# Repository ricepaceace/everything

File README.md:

# everything
Each folder in this directory contains all the files for the separate areas of our project.
matlab_algorithms     contains all of the data and matlab code for running simulations of our developing algorithm
analogTest            contains the design of our artificial anaolg input generator
Arduino               contains all the code and test data used by the Arduino microcontroller
preprocessor_harware  contains the design of our preprocessor boards
xilinx_design         contains the FPGA design

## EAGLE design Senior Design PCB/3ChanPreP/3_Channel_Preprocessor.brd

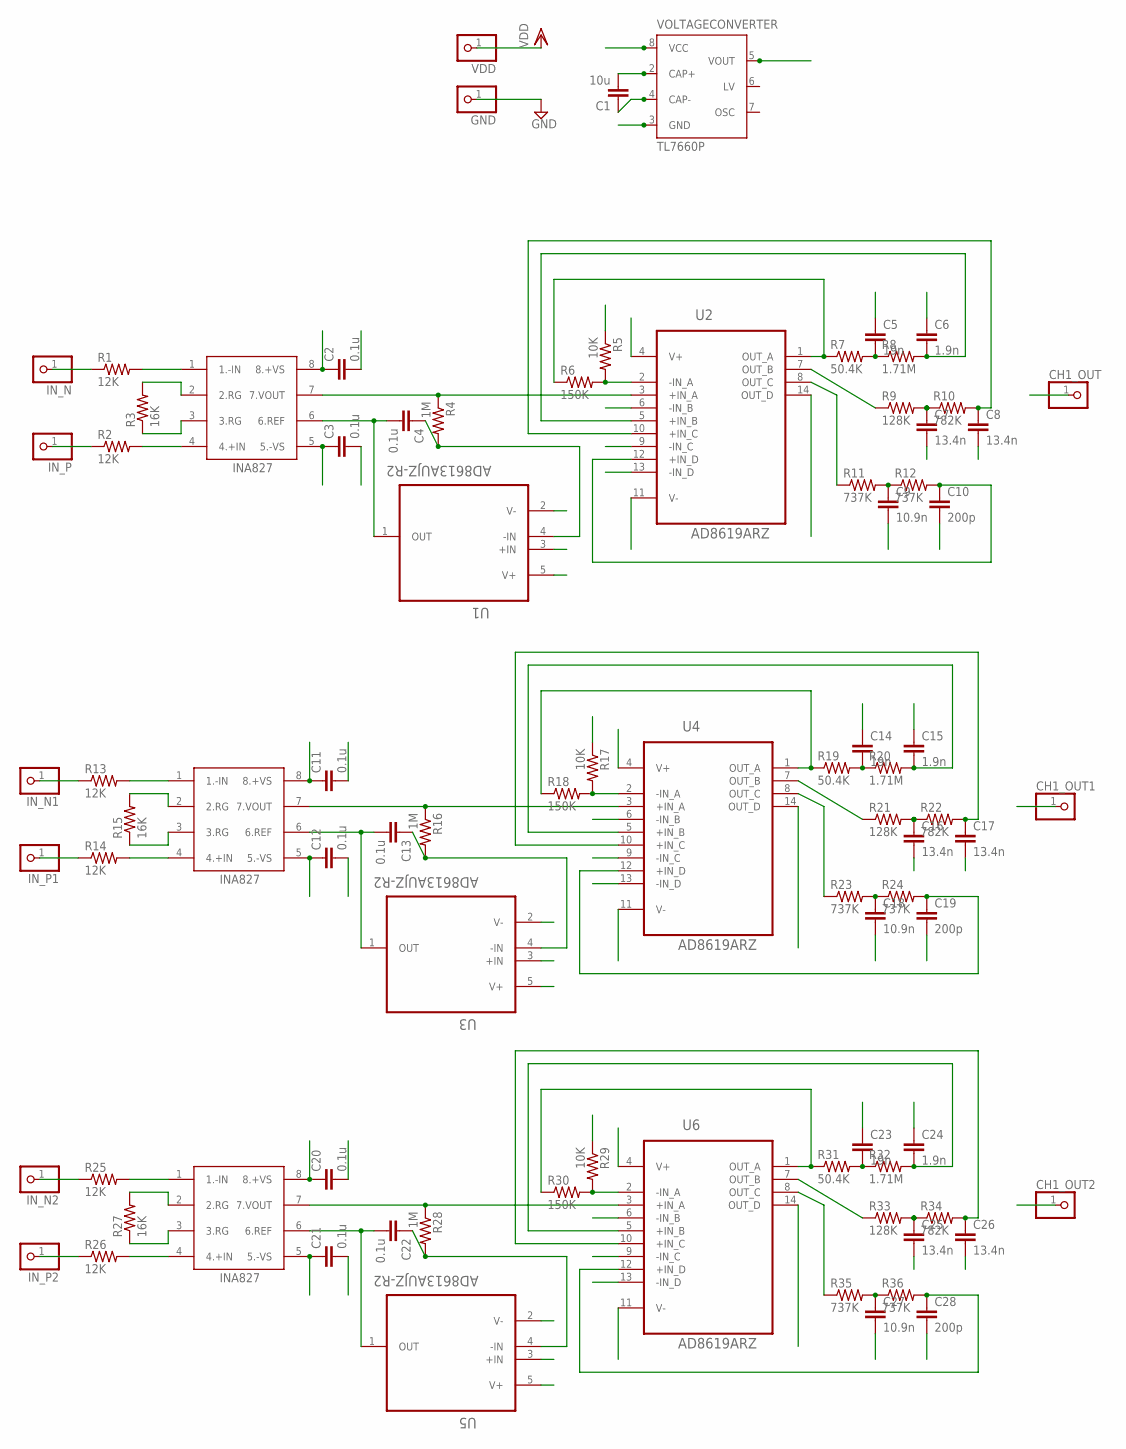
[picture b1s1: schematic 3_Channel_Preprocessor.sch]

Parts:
C1: 10u; C1206
C2, C3, C4, C11, C12, C13, C20, C21, C22: 0.1u; C1206
C5, C14, C23: 19n; C1206
C6, C15, C24: 1.9n; C1206
C7, C8, C16, C17, C25, C26: 13.4n; C1206
C9, C18, C27: 10.9n; C1206
C10, C19, C28: 200p; C1206
CH1_OUT, CH1_OUT1, CH1_OUT2: PINHD-1X1; 1X01
GND: PINHD-1X1; 1X01
INA1: INA827
IN_N, IN_N1, IN_N2: PINHD-1X1; 1X01
IN_P, IN_P1, IN_P2: PINHD-1X1; 1X01
R1, R2, R13, R14, R25, R26: 12K; M1206
R3, R15, R27: 16K; M1206
R4, R16, R28: 1M; M1206
R5, R17, R29: 10K; M1206
R6, R18, R30: 150K; M1206
R7, R19, R31: 50.4K; M1206
R8, R20, R32: 1.71M; M1206
R9, R21, R33: 128K; M1206
R10, R22, R34: 782K; M1206
R11, R12, R23, R24, R35, R36: 737K; M1206
U1, U3, U5: AD8613AUJZ-R2; SOT95P280X100-5N
U2, U4, U6: AD8619ARZ; SOIC127P600X175-14N
U$2, U$3: INA827
VDD: PINHD-1X1; 1X01
VOLTAGECONVERTER: TL7660P; DIL08

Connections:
GND: C2.2, C3.2, C6.1, C8.2, C10.2, C11.2, C12.2, C15.1, C17.2, C19.2, C20.2, C21.2, C24.1, C26.2, C28.2, GND.1, R5.1, R17.1, R29.1, U1.3 (+IN), U3.3 (+IN), U5.3 (+IN), VOLTAGECONVERTER.3 (GND)
IN_N: IN_N.1, R1.1
IN_N1: IN_N1.1, R13.1
IN_N2: IN_N2.1, R25.1
IN_P: IN_P.1, R2.1
IN_P1: IN_P1.1, R14.1
IN_P2: IN_P2.1, R26.1
unnamed: C1.2, VOLTAGECONVERTER.2 (CAP+)
unnamed: C1.1, VOLTAGECONVERTER.4 (CAP-)
unnamed: INA1.1 (1.-IN), R1.2
unnamed: INA1.4 (4.+IN), R2.2
unnamed: INA1.2 (2.RG), R3.2
unnamed: INA1.3 (3.RG), R3.1
unnamed: C4.2, INA1.6 (6.REF), U1.1 (OUT)
unnamed: INA1.7 (7.VOUT), R4.1, U2.3 (+IN_A)
unnamed: C4.1, R4.2, U1.4 (-IN)
unnamed: R5.2, R6.2, U2.2 (-IN_A)
unnamed: R6.1, R7.1, U2.1 (OUT_A)
unnamed: C5.2, R7.2, R8.1
unnamed: C6.2, R8.2, U2.5 (+IN_B)
unnamed: C7.1, R9.2, R10.1
unnamed: C8.1, R10.2, U2.10 (+IN_C)
unnamed: C9.1, R11.2, R12.1
unnamed: C10.1, R12.2, U2.12 (+IN_D)
unnamed: R13.2, U$2.1 (1.-IN)
unnamed: R14.2, U$2.4 (4.+IN)
unnamed: R15.2, U$2.2 (2.RG)
unnamed: R15.1, U$2.3 (3.RG)
unnamed: C13.2, U3.1 (OUT), U$2.6 (6.REF)
unnamed: R16.1, U4.3 (+IN_A), U$2.7 (7.VOUT)
unnamed: C13.1, R16.2, U3.4 (-IN)
unnamed: R17.2, R18.2, U4.2 (-IN_A)
unnamed: R18.1, R19.1, U4.1 (OUT_A)
unnamed: C14.2, R19.2, R20.1
unnamed: C15.2, R20.2, U4.5 (+IN_B)
unnamed: C16.1, R21.2, R22.1
unnamed: C17.1, R22.2, U4.10 (+IN_C)
unnamed: C18.1, R23.2, R24.1
unnamed: C19.1, R24.2, U4.12 (+IN_D)
unnamed: R25.2, U$3.1 (1.-IN)
unnamed: R26.2, U$3.4 (4.+IN)
unnamed: R27.2, U$3.2 (2.RG)
unnamed: R27.1, U$3.3 (3.RG)
unnamed: C22.2, U5.1 (OUT), U$3.6 (6.REF)
unnamed: R28.1, U6.3 (+IN_A), U$3.7 (7.VOUT)
unnamed: C22.1, R28.2, U5.4 (-IN)
unnamed: R29.2, R30.2, U6.2 (-IN_A)
unnamed: R30.1, R31.1, U6.1 (OUT_A)
unnamed: C23.2, R31.2, R32.1
unnamed: C24.2, R32.2, U6.5 (+IN_B)
unnamed: C25.1, R33.2, R34.1
unnamed: C26.1, R34.2, U6.10 (+IN_C)
unnamed: C27.1, R35.2, R36.1
unnamed: C28.1, R36.2, U6.12 (+IN_D)
OUT_B: C5.1, R9.1, U2.6 (-IN_B), U2.7 (OUT_B)
OUT_B1: C14.1, R21.1, U4.6 (-IN_B), U4.7 (OUT_B)
OUT_B2: C23.1, R33.1, U6.6 (-IN_B), U6.7 (OUT_B)
OUT_C: C7.2, R11.1, U2.8 (OUT_C), U2.9 (-IN_C)
OUT_C1: C16.2, R23.1, U4.8 (OUT_C), U4.9 (-IN_C)
OUT_C2: C25.2, R35.1, U6.8 (OUT_C), U6.9 (-IN_C)
OUT_D: C9.2, CH1_OUT.1, U2.13 (-IN_D), U2.14 (OUT_D)
OUT_D1: C18.2, CH1_OUT1.1, U4.13 (-IN_D), U4.14 (OUT_D)
OUT_D2: C27.2, CH1_OUT2.1, U6.13 (-IN_D), U6.14 (OUT_D)
VDD: C2.1, C11.1, C20.1, INA1.8 (8.+VS), U1.5 (V+), U2.4 (V+), U3.5 (V+), U4.4 (V+), U5.5 (V+), U6.4 (V+), U$2.8 (8.+VS), U$3.8 (8.+VS), VDD.1, VOLTAGECONVERTER.8 (VCC)
VDD-: C3.1, C12.1, C21.1, INA1.5 (5.-VS), U1.2 (V-), U2.11 (V-), U3.2 (V-), U4.11 (V-), U5.2 (V-), U6.11 (V-), U$2.5 (5.-VS), U$3.5 (5.-VS), VOLTAGECONVERTER.5 (VOUT)

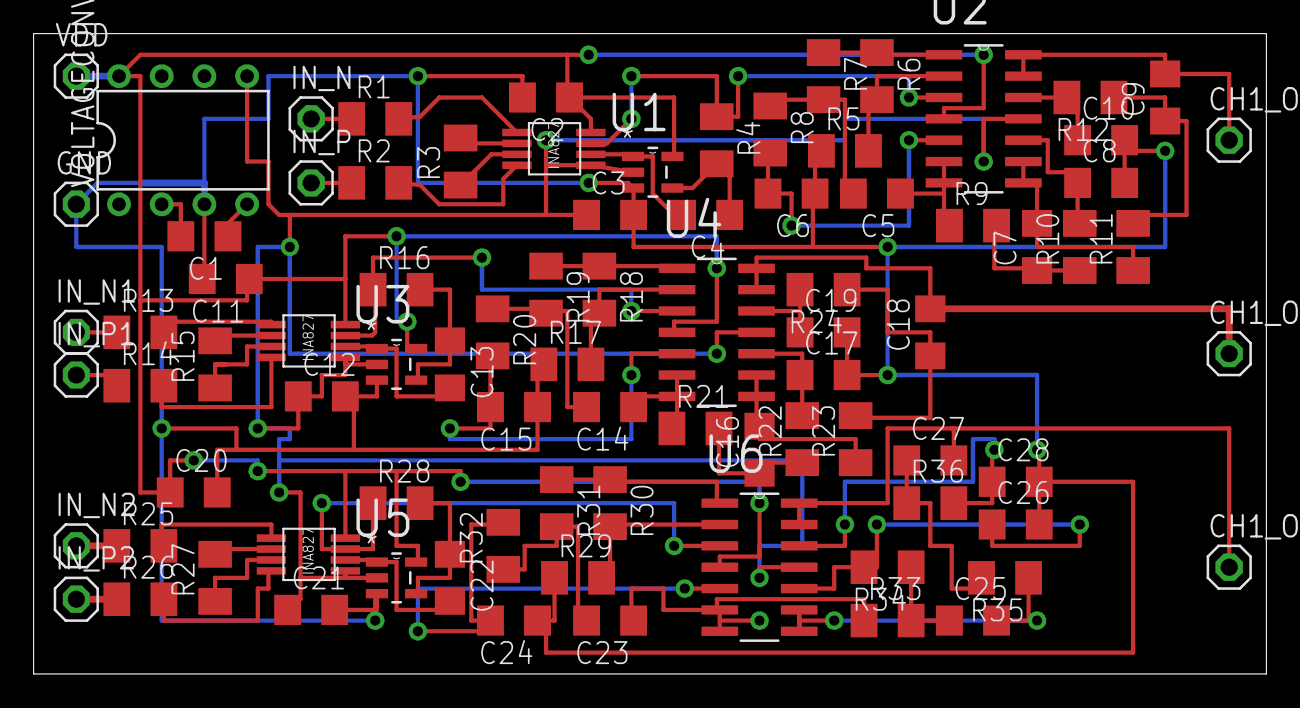
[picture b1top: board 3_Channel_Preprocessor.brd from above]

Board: 2 copper layers, 73.3 x 38.1 mm, 85 parts (0 on the bottom side), 65 nets.

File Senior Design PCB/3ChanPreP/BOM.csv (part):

"Part";"Value";"Device";"Package";"Description";"AVAILABILITY";"DESCRIPTION";"MF";"MP";"MPN";"OC_FARNELL";"OC_NEWARK";"PACKAGE";"PRICE";
"C1";"10u";"C-EUC1206";"C1206";"CAPACITOR, European symbol";"";"";"";"";"";"";"";"";"";
"C2";"0.1u";"C-EUC1206";"C1206";"CAPACITOR, European symbol";"";"";"";"";"";"";"";"";"";
"C3";"0.1u";"C-EUC1206";"C1206";"CAPACITOR, European symbol";"";"";"";"";"";"";"";"";"";
"C4";"0.1u";"C-EUC1206";"C1206";"CAPACITOR, European symbol";"";"";"";"";"";"";"";"";"";
"C5";"19n";"C-EUC1206";"C1206";"CAPACITOR, European symbol";"";"";"";"";"";"";"";"";"";
"C6";"1.9n";"C-EUC1206";"C1206";"CAPACITOR, European symbol";"";"";"";"";"";"";"";"";"";
"C7";"13.4n";"C-EUC1206";"C1206";"CAPACITOR, European symbol";"";"";"";"";"";"";"";"";"";
"C8";"13.4n";"C-EUC1206";"C1206";"CAPACITOR, European symbol";"";"";"";"";"";"";"";"";"";
"C9";"10.9n";"C-EUC1206";"C1206";"CAPACITOR, European symbol";"";"";"";"";"";"";"";"";"";
"C10";"200p";"C-EUC1206";"C1206";"CAPACITOR, European symbol";"";"";"";"";"";"";"";"";"";
"C11";"0.1u";"C-EUC1206";"C1206";"CAPACITOR, European symbol";"";"";"";"";"";"";"";"";"";
"C12";"0.1u";"C-EUC1206";"C1206";"CAPACITOR, European symbol";"";"";"";"";"";"";"";"";"";
"C13";"0.1u";"C-EUC1206";"C1206";"CAPACITOR, European symbol";"";"";"";"";"";"";"";"";"";
"C14";"19n";"C-EUC1206";"C1206";"CAPACITOR, European symbol";"";"";"";"";"";"";"";"";"";
"C15";"1.9n";"C-EUC1206";"C1206";"CAPACITOR, European symbol";"";"";"";"";"";"";"";"";"";
"C16";"13.4n";"C-EUC1206";"C1206";"CAPACITOR, European symbol";"";"";"";"";"";"";"";"";"";
"C17";"13.4n";"C-EUC1206";"C1206";"CAPACITOR, European symbol";"";"";"";"";"";"";"";"";"";
"C18";"10.9n";"C-EUC1206";"C1206";"CAPACITOR, European symbol";"";"";"";"";"";"";"";"";"";
"C19";"200p";"C-EUC1206";"C1206";"CAPACITOR, European symbol";"";"";"";"";"";"";"";"";"";
"C20";"0.1u";"C-EUC1206";"C1206";"CAPACITOR, European symbol";"";"";"";"";"";"";"";"";"";
"C21";"0.1u";"C-EUC1206";"C1206";"CAPACITOR, European symbol";"";"";"";"";"";"";"";"";"";
"C22";"0.1u";"C-EUC1206";"C1206";"CAPACITOR, European symbol";"";"";"";"";"";"";"";"";"";
"C23";"19n";"C-EUC1206";"C1206";"CAPACITOR, European symbol";"";"";"";"";"";"";"";"";"";
"C24";"1.9n";"C-EUC1206";"C1206";"CAPACITOR, European symbol";"";"";"";"";"";"";"";"";"";
"C25";"13.4n";"C-EUC1206";"C1206";"CAPACITOR, European symbol";"";"";"";"";"";"";"";"";"";
"C26";"13.4n";"C-EUC1206";"C1206";"CAPACITOR, European symbol";"";"";"";"";"";"";"";"";"";
"C27";"10.9n";"C-EUC1206";"C1206";"CAPACITOR, European symbol";"";"";"";"";"";"";"";"";"";
"C28";"200p";"C-EUC1206";"C1206";"CAPACITOR, European symbol";"";"";"";"";"";"";"";"";"";
"CH0_OUT";"";"PINHD-1X1";"1X01";"PIN HEADER";"";"";"";"";"";"";"";"";"";
"CH1_OUT";"";"PINHD-1X1";"1X01";"PIN HEADER";"";"";"";"";"";"";"";"";"";
"CH2_OUT";"";"PINHD-1X1";"1X01";"PIN HEADER";"";"";"";"";"";"";"";"";"";
"GND";"";"PINHD-1X1";"1X01";"PIN HEADER";"";"";"";"";"";"";"";"";"";
"IN0+";"";"PINHD-1X1";"1X01";"PIN HEADER";"";"";"";"";"";"";"";"";"";
"IN0-";"";"PINHD-1X1";"1X01";"PIN HEADER";"";"";"";"";"";"";"";"";"";
"IN1+";"";"PINHD-1X1";"1X01";"PIN HEADER";"";"";"";"";"";"";"";"";"";
"IN1-";"";"PINHD-1X1";"1X01";"PIN HEADER";"";"";"";"";"";"";"";"";"";
"IN2+";"";"PINHD-1X1";"1X01";"PIN HEADER";"";"";"";"";"";"";"";"";"";
"IN2-";"";"PINHD-1X1";"1X01";"PIN HEADER";"";"";"";"";"";"";"";"";"";
"INA1";"INA827";"INA827";"INA827";"";"";"";"";"";"";"";"";"";"";
"R1";"12K";"R-US_M1206";"M1206";"RESISTOR, American symbol";"";"";"";"";"";"";"";"";"";
"R2";"12K";"R-US_M1206";"M1206";"RESISTOR, American symbol";"";"";"";"";"";"";"";"";"";
"R3";"16K";"R-US_M1206";"M1206";"RESISTOR, American symbol";"";"";"";"";"";"";"";"";"";
"R4";"1M";"R-US_M1206";"M1206";"RESISTOR, American symbol";"";"";"";"";"";"";"";"";"";
"R5";"10K";"R-US_M1206";"M1206";"RESISTOR, American symbol";"";"";"";"";"";"";"";"";"";
"R6";"150K";"R-US_M1206";"M1206";"RESISTOR, American symbol";"";"";"";"";"";"";"";"";"";
"R7";"50.4K";"R-US_M1206";"M1206";"RESISTOR, American symbol";"";"";"";"";"";"";"";"";"";
"R8";"1.71M";"R-US_M1206";"M1206";"RESISTOR, American symbol";"";"";"";"";"";"";"";"";"";
"R9";"128K";"R-US_M1206";"M1206";"RESISTOR, American symbol";"";"";"";"";"";"";"";"";"";
"R10";"782K";"R-US_M1206";"M1206";"RESISTOR, American symbol";"";"";"";"";"";"";"";"";"";
"R11";"737K";"R-US_M1206";"M1206";"RESISTOR, American symbol";"";"";"";"";"";"";"";"";"";
"R12";"737K";"R-US_M1206";"M1206";"RESISTOR, American symbol";"";"";"";"";"";"";"";"";"";
"R13";"12K";"R-US_M1206";"M1206";"RESISTOR, American symbol";"";"";"";"";"";"";"";"";"";
"R14";"12K";"R-US_M1206";"M1206";"RESISTOR, American symbol";"";"";"";"";"";"";"";"";"";
"R15";"16K";"R-US_M1206";"M1206";"RESISTOR, American symbol";"";"";"";"";"";"";"";"";"";
"R16";"1M";"R-US_M1206";"M1206";"RESISTOR, American symbol";"";"";"";"";"";"";"";"";"";
"R17";"10K";"R-US_M1206";"M1206";"RESISTOR, American symbol";"";"";"";"";"";"";"";"";"";
"R18";"150K";"R-US_M1206";"M1206";"RESISTOR, American symbol";"";"";"";"";"";"";"";"";"";
"R19";"50.4K";"R-US_M1206";"M1206";"RESISTOR, American symbol";"";"";"";"";"";"";"";"";"";
"R20";"1.71M";"R-US_M1206";"M1206";"RESISTOR, American symbol";"";"";"";"";"";"";"";"";"";
"R21";"128K";"R-US_M1206";"M1206";"RESISTOR, American symbol";"";"";"";"";"";"";"";"";"";
"R22";"782K";"R-US_M1206";"M1206";"RESISTOR, American symbol";"";"";"";"";"";"";"";"";"";
"R23";"737K";"R-US_M1206";"M1206";"RESISTOR, American symbol";"";"";"";"";"";"";"";"";"";
"R24";"737K";"R-US_M1206";"M1206";"RESISTOR, American symbol";"";"";"";"";"";"";"";"";"";
"R25";"12K";"R-US_M1206";"M1206";"RESISTOR, American symbol";"";"";"";"";"";"";"";"";"";
"R26";"12K";"R-US_M1206";"M1206";"RESISTOR, American symbol";"";"";"";"";"";"";"";"";"";
"R27";"16K";"R-US_M1206";"M1206";"RESISTOR, American symbol";"";"";"";"";"";"";"";"";"";
"R28";"1M";"R-US_M1206";"M1206";"RESISTOR, American symbol";"";"";"";"";"";"";"";"";"";
"R29";"10K";"R-US_M1206";"M1206";"RESISTOR, American symbol";"";"";"";"";"";"";"";"";"";
"R30";"150K";"R-US_M1206";"M1206";"RESISTOR, American symbol";"";"";"";"";"";"";"";"";"";
"R31";"50.4K";"R-US_M1206";"M1206";"RESISTOR, American symbol";"";"";"";"";"";"";"";"";"";
"R32";"1.71M";"R-US_M1206";"M1206";"RESISTOR, American symbol";"";"";"";"";"";"";"";"";"";
"R33";"128K";"R-US_M1206";"M1206";"RESISTOR, American symbol";"";"";"";"";"";"";"";"";"";
"R34";"782K";"R-US_M1206";"M1206";"RESISTOR, American symbol";"";"";"";"";"";"";"";"";"";
"R35";"737K";"R-US_M1206";"M1206";"RESISTOR, American symbol";"";"";"";"";"";"";"";"";"";
"R36";"737K";"R-US_M1206";"M1206";"RESISTOR, American symbol";"";"";"";"";"";"";"";"";"";
"U$2";"INA827";"INA827";"INA827";"";"";"";"";"";"";"";"";"";"";
"U$3";"INA827";"INA827";"INA827";"";"";"";"";"";"";"";"";"";"";
"U1";"AD8613AUJZ-R2";"AD8613AUJZ-R2";"SOT95P280X100-5N";"Input/Output Operational Amplifiers";"Good";"OPERATIONAL AMPLIFIER, 400KHZ, 0.1V/ us, TSOT-23-5";"Analog Devices";"AD8613AUJZ-R2";"";"";"";"SOT-23-5 Analog Devices";"1.17 USD";
"U2";"AD8619ARZ";"AD8619ARZ";"SOIC127P600X175-14N";"Operational Amplifiers";"Good";"OP Amp Quad GP R-R I/O ???}2.5V/5V 14-Pin SOIC N Tube";"Analog Devices";"AD8619ARZ";"";"";"";"SOIC-14 Analog Devices";"1.96 USD";
"U3";"AD8613AUJZ-R2";"AD8613AUJZ-R2";"SOT95P280X100-5N";"Input/Output Operational Amplifiers";"Good";"OPERATIONAL AMPLIFIER, 400KHZ, 0.1V/ us, TSOT-23-5";"Analog Devices";"AD8613AUJZ-R2";"";"";"";"SOT-23-5 Analog Devices";"1.17 USD";
"U4";"AD8619ARZ";"AD8619ARZ";"SOIC127P600X175-14N";"Operational Amplifiers";"Good";"OP Amp Quad GP R-R I/O ???}2.5V/5V 14-Pin SOIC N Tube";"Analog Devices";"AD8619ARZ";"";"";"";"SOIC-14 Analog Devices";"1.96 USD";
"U5";"AD8613AUJZ-R2";"AD8613AUJZ-R2";"SOT95P280X100-5N";"Input/Output Operational Amplifiers";"Good";"OPERATIONAL AMPLIFIER, 400KHZ, 0.1V/ us, TSOT-23-5";"Analog Devices";"AD8613AUJZ-R2";"";"";"";"SOT-23-5 Analog Devices";"1.17 USD";
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
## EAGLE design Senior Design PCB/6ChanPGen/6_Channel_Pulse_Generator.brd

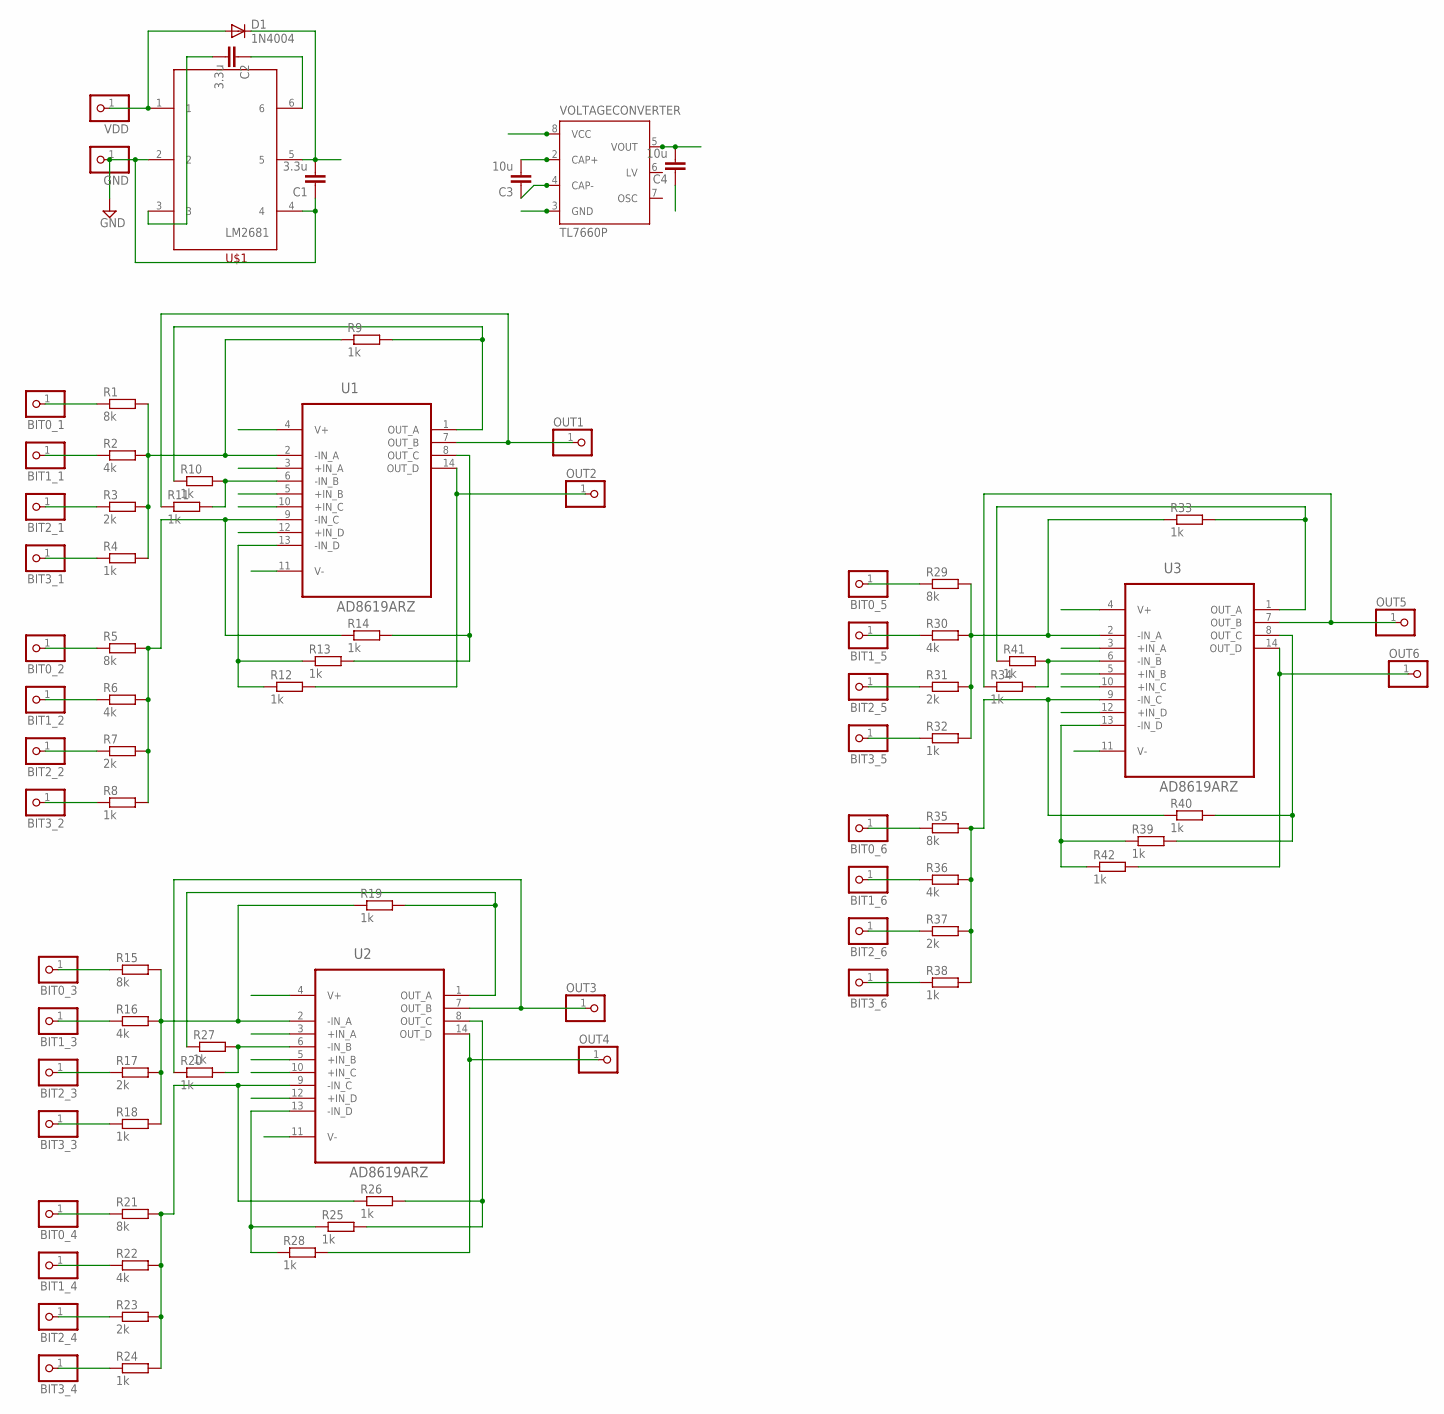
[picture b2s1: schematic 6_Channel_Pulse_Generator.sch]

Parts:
BIT0_1, BIT0_2, BIT0_3, BIT0_4, BIT0_5, BIT0_6, BIT1_1, BIT1_2, BIT1_3, BIT1_4, BIT1_5, BIT1_6, BIT2_1, BIT2_2, BIT2_3, BIT2_4, BIT2_5, BIT2_6, BIT3_1, BIT3_2, BIT3_3, BIT3_4, BIT3_5, BIT3_6: PINHD-1X1; 1X01
C1, C2: 3.3u; C1206
C3, C4: 10u; C1206
D1: 1N4004; DO41-10
GND: PINHD-1X1; 1X01
OUT1, OUT2, OUT3, OUT4, OUT5, OUT6: PINHD-1X1; 1X01
R1, R5, R15, R21, R29, R35: 8k; M1206
R2, R6, R16, R22, R30, R36: 4k; M1206
R3, R7, R17, R23, R31, R37: 2k; M1206
R4, R8, R9, R10, R11, R12, R13, R14, R18, R19, R20, R24, R25, R26, R27, R28, R32, R33, R34, R38, R39, R40, R41, R42: 1k; M1206
U1, U2, U3: AD8619ARZ; SOIC127P600X175-14N
U$1: LM2681
VDD: PINHD-1X1; 1X01
VOLTAGECONVERTER: TL7660P; DIL08

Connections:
GND: C1.1, C4.1, GND.1, U1.3 (+IN_A), U1.5 (+IN_B), U1.10 (+IN_C), U1.12 (+IN_D), U2.3 (+IN_A), U2.5 (+IN_B), U2.10 (+IN_C), U2.12 (+IN_D), U3.3 (+IN_A), U3.5 (+IN_B), U3.10 (+IN_C), U3.12 (+IN_D), U$1.2, U$1.4, VOLTAGECONVERTER.3 (GND)
unnamed: BIT0_1.1, R1.1
unnamed: C2.2, U$1.3
unnamed: C3.2, VOLTAGECONVERTER.2 (CAP+)
unnamed: C3.1, VOLTAGECONVERTER.4 (CAP-)
unnamed: BIT1_1.1, R2.1
unnamed: BIT2_1.1, R3.1
unnamed: BIT3_1.1, R4.1
unnamed: BIT0_2.1, R5.1
unnamed: BIT2_2.1, R7.1
unnamed: BIT3_2.1, R8.1
unnamed: BIT1_2.1, R6.1
unnamed: R1.2, R2.2, R3.2, R4.2, R9.1, U1.2 (-IN_A)
unnamed: R5.2, R6.2, R7.2, R8.2, R14.1, U1.9 (-IN_C)
unnamed: R13.2, R14.2, U1.8 (OUT_C)
unnamed: OUT2.1, R12.2, U1.14 (OUT_D)
unnamed: R12.1, R13.1, U1.13 (-IN_D)
unnamed: R9.2, R10.1, U1.1 (OUT_A)
unnamed: OUT1.1, R11.1, U1.7 (OUT_B)
unnamed: R10.2, R11.2, U1.6 (-IN_B)
unnamed: C2.1, U$1.6
unnamed: BIT0_3.1, R15.1
unnamed: BIT2_3.1, R17.1
unnamed: BIT3_3.1, R18.1
unnamed: BIT1_3.1, R16.1
unnamed: BIT0_4.1, R21.1
unnamed: BIT2_4.1, R23.1
unnamed: BIT3_4.1, R24.1
unnamed: BIT1_4.1, R22.1
unnamed: R15.2, R16.2, R17.2, R18.2, R19.1, U2.2 (-IN_A)
unnamed: R19.2, R27.1, U2.1 (OUT_A)
unnamed: OUT3.1, R20.1, U2.7 (OUT_B)
unnamed: R20.2, R27.2, U2.6 (-IN_B)
unnamed: R21.2, R22.2, R23.2, R24.2, R26.1, U2.9 (-IN_C)
unnamed: R25.2, R26.2, U2.8 (OUT_C)
unnamed: R25.1, R28.1, U2.13 (-IN_D)
unnamed: OUT4.1, R28.2, U2.14 (OUT_D)
unnamed: BIT0_5.1, R29.1
unnamed: BIT2_5.1, R31.1
unnamed: BIT3_5.1, R32.1
unnamed: BIT1_5.1, R30.1
unnamed: BIT0_6.1, R35.1
unnamed: BIT2_6.1, R37.1
unnamed: BIT3_6.1, R38.1
unnamed: BIT1_6.1, R36.1
unnamed: R29.2, R30.2, R31.2, R32.2, R33.1, U3.2 (-IN_A)
unnamed: R33.2, R41.1, U3.1 (OUT_A)
unnamed: OUT5.1, R34.1, U3.7 (OUT_B)
unnamed: R34.2, R41.2, U3.6 (-IN_B)
unnamed: R35.2, R36.2, R37.2, R38.2, R40.1, U3.9 (-IN_C)
unnamed: R39.2, R40.2, U3.8 (OUT_C)
unnamed: R39.1, R42.1, U3.13 (-IN_D)
unnamed: OUT6.1, R42.2, U3.14 (OUT_D)
VDD: C1.2, D1.C, U1.4 (V+), U2.4 (V+), U3.4 (V+), U$1.5, VOLTAGECONVERTER.8 (VCC)
VDD-: C4.2, U1.11 (V-), U2.11 (V-), U3.11 (V-), VOLTAGECONVERTER.5 (VOUT)
VDD_3.3: D1.A, U$1.1, VDD.1

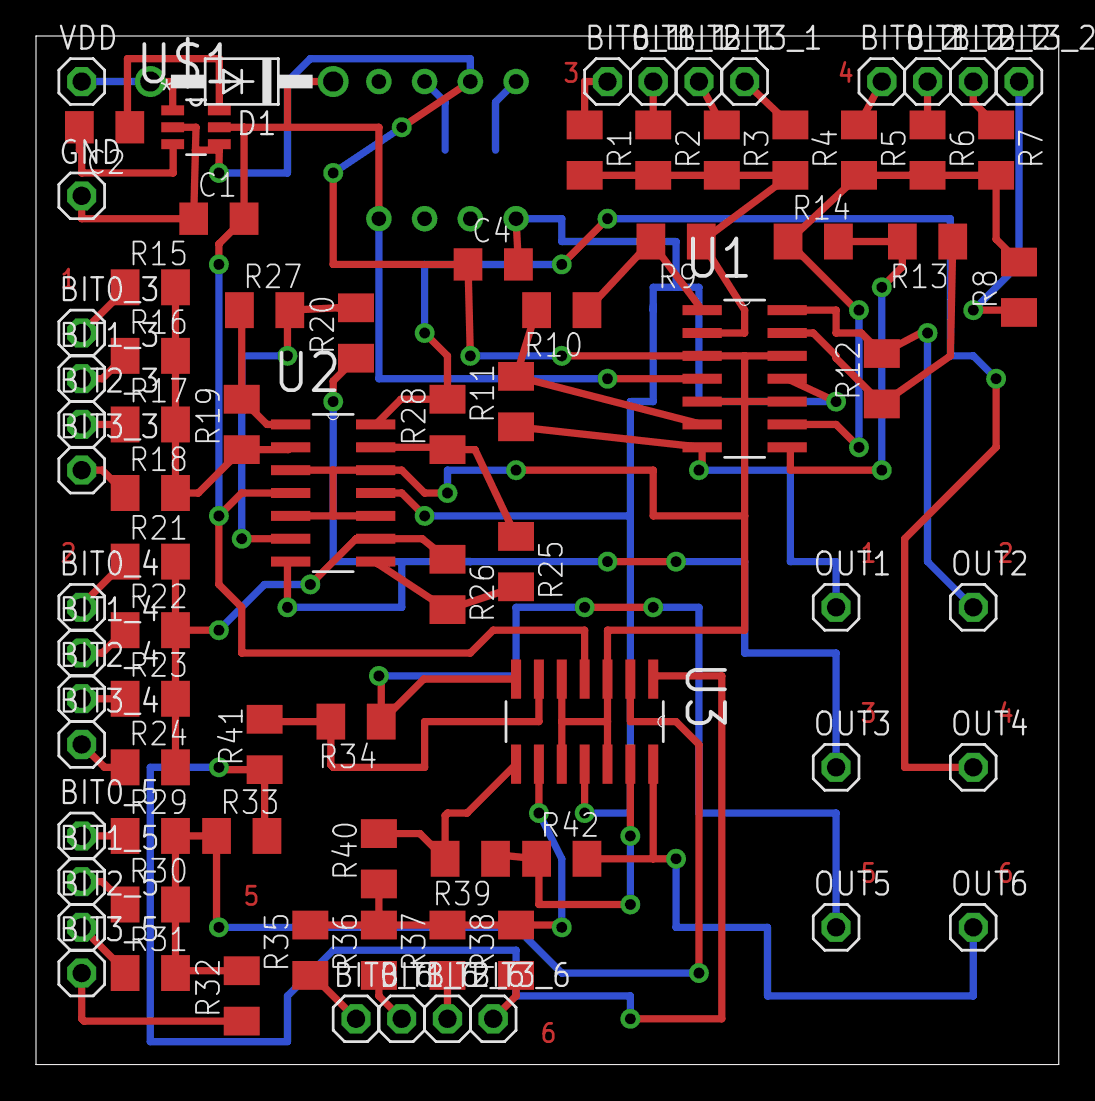
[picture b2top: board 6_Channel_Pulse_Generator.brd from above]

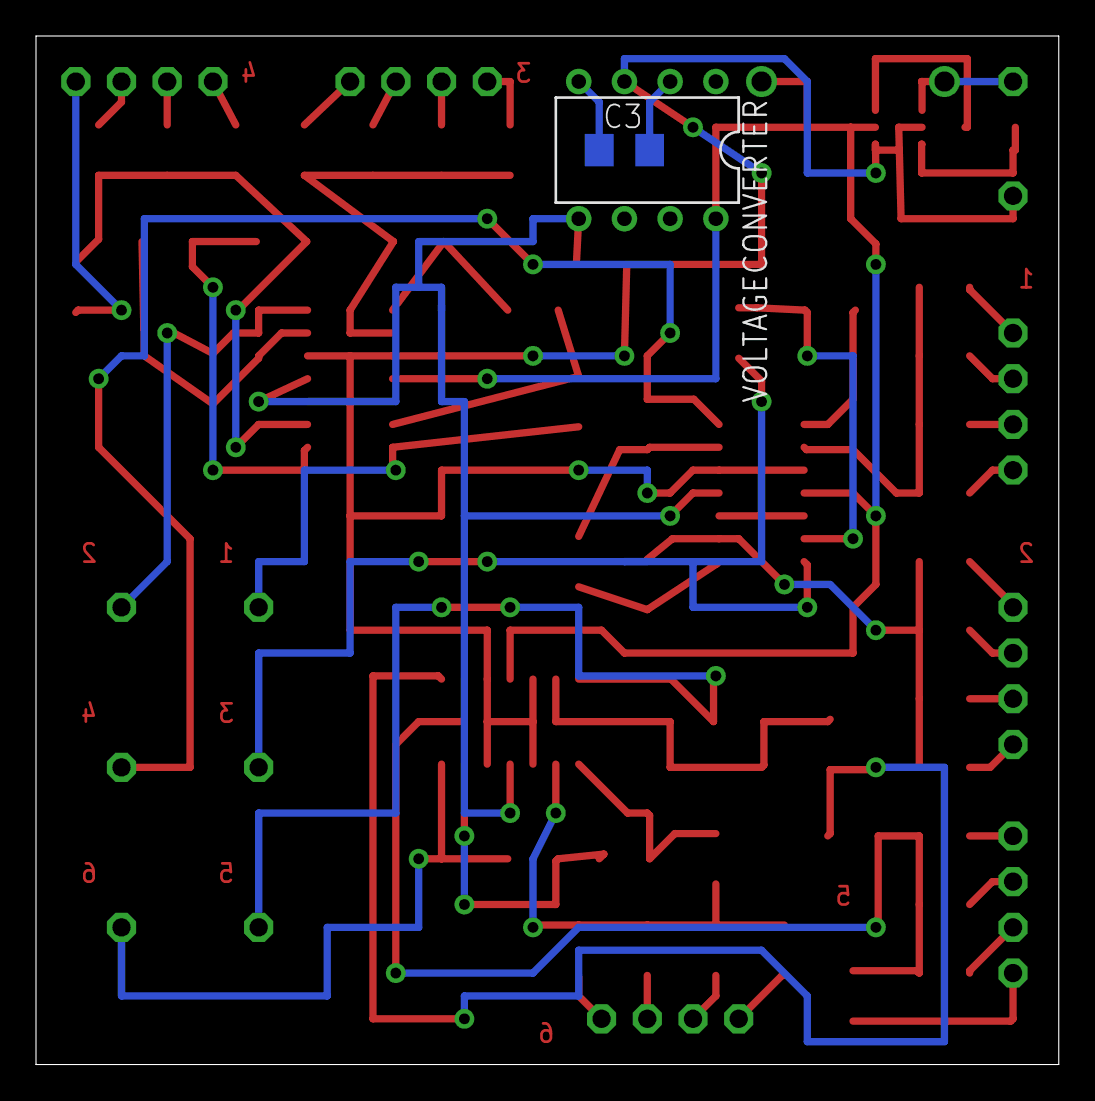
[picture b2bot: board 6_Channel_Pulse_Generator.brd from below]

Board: 2 copper layers, 56.8 x 57.1 mm, 84 parts (2 on the bottom side), 56 nets.

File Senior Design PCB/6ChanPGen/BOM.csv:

"Part";"Value";"Device";"Package";"Description";"AVAILABILITY";"DESCRIPTION";"MF";"MP";"MPN";"OC_FARNELL";"OC_NEWARK";"PACKAGE";"PRICE";
"BIT0_1";"a0";"PINHD-1X1";"1X01";"PIN HEADER";"";"";"";"";"";"";"";"";"";
"BIT0_2";"b0";"PINHD-1X1";"1X01";"PIN HEADER";"";"";"";"";"";"";"";"";"";
"BIT0_3";"c0";"PINHD-1X1";"1X01";"PIN HEADER";"";"";"";"";"";"";"";"";"";
"BIT0_4";"d0";"PINHD-1X1";"1X01";"PIN HEADER";"";"";"";"";"";"";"";"";"";
"BIT0_5";"e0";"PINHD-1X1";"1X01";"PIN HEADER";"";"";"";"";"";"";"";"";"";
"BIT0_6";"f0";"PINHD-1X1";"1X01";"PIN HEADER";"";"";"";"";"";"";"";"";"";
"BIT1_1";"a1";"PINHD-1X1";"1X01";"PIN HEADER";"";"";"";"";"";"";"";"";"";
"BIT1_2";"b1";"PINHD-1X1";"1X01";"PIN HEADER";"";"";"";"";"";"";"";"";"";
"BIT1_3";"c1";"PINHD-1X1";"1X01";"PIN HEADER";"";"";"";"";"";"";"";"";"";
"BIT1_4";"d1";"PINHD-1X1";"1X01";"PIN HEADER";"";"";"";"";"";"";"";"";"";
"BIT1_5";"e1";"PINHD-1X1";"1X01";"PIN HEADER";"";"";"";"";"";"";"";"";"";
"BIT1_6";"f1";"PINHD-1X1";"1X01";"PIN HEADER";"";"";"";"";"";"";"";"";"";
"BIT2_1";"a2";"PINHD-1X1";"1X01";"PIN HEADER";"";"";"";"";"";"";"";"";"";
"BIT2_2";"b2";"PINHD-1X1";"1X01";"PIN HEADER";"";"";"";"";"";"";"";"";"";
"BIT2_3";"c2";"PINHD-1X1";"1X01";"PIN HEADER";"";"";"";"";"";"";"";"";"";
"BIT2_4";"d2";"PINHD-1X1";"1X01";"PIN HEADER";"";"";"";"";"";"";"";"";"";
"BIT2_5";"e2";"PINHD-1X1";"1X01";"PIN HEADER";"";"";"";"";"";"";"";"";"";
"BIT2_6";"f2";"PINHD-1X1";"1X01";"PIN HEADER";"";"";"";"";"";"";"";"";"";
"BIT3_1";"a3";"PINHD-1X1";"1X01";"PIN HEADER";"";"";"";"";"";"";"";"";"";
"BIT3_2";"b3";"PINHD-1X1";"1X01";"PIN HEADER";"";"";"";"";"";"";"";"";"";
"BIT3_3";"c3";"PINHD-1X1";"1X01";"PIN HEADER";"";"";"";"";"";"";"";"";"";
"BIT3_4";"d3";"PINHD-1X1";"1X01";"PIN HEADER";"";"";"";"";"";"";"";"";"";
"BIT3_5";"e3";"PINHD-1X1";"1X01";"PIN HEADER";"";"";"";"";"";"";"";"";"";
"BIT3_6";"f3";"PINHD-1X1";"1X01";"PIN HEADER";"";"";"";"";"";"";"";"";"";
"C1";"3.3u";"C-EUC1206";"C1206";"CAPACITOR, European symbol";"";"";"";"";"";"";"";"";"";
"C2";"3.3u";"C-EUC1206";"C1206";"CAPACITOR, European symbol";"";"";"";"";"";"";"";"";"";
"C3";"10u";"C-EUC1206";"C1206";"CAPACITOR, European symbol";"";"";"";"";"";"";"";"";"";
"C4";"10u";"C-EUC1206";"C1206";"CAPACITOR, European symbol";"";"";"";"";"";"";"";"";"";
"D1";"1N4004";"1N4004";"DO41-10";"DIODE";"";"";"";"";"";"";"";"";"";
"GND";"";"PINHD-1X1";"1X01";"PIN HEADER";"";"";"";"";"";"";"";"";"";
"OUTA";"";"PINHD-1X1";"1X01";"PIN HEADER";"";"";"";"";"";"";"";"";"";
"OUTB";"";"PINHD-1X1";"1X01";"PIN HEADER";"";"";"";"";"";"";"";"";"";
"OUTC";"";"PINHD-1X1";"1X01";"PIN HEADER";"";"";"";"";"";"";"";"";"";
"OUTD";"";"PINHD-1X1";"1X01";"PIN HEADER";"";"";"";"";"";"";"";"";"";
"OUTE";"";"PINHD-1X1";"1X01";"PIN HEADER";"";"";"";"";"";"";"";"";"";
"OUTF";"";"PINHD-1X1";"1X01";"PIN HEADER";"";"";"";"";"";"";"";"";"";
"R1";"8k";"R-EU_M1206";"M1206";"RESISTOR, European symbol";"";"";"";"";"";"";"";"";"";
"R2";"4k";"R-EU_M1206";"M1206";"RESISTOR, European symbol";"";"";"";"";"";"";"";"";"";
"R3";"2k";"R-EU_M1206";"M1206";"RESISTOR, European symbol";"";"";"";"";"";"";"";"";"";
"R4";"1k";"R-EU_M1206";"M1206";"RESISTOR, European symbol";"";"";"";"";"";"";"";"";"";
"R5";"8k";"R-EU_M1206";"M1206";"RESISTOR, European symbol";"";"";"";"";"";"";"";"";"";
"R6";"4k";"R-EU_M1206";"M1206";"RESISTOR, European symbol";"";"";"";"";"";"";"";"";"";
"R7";"2k";"R-EU_M1206";"M1206";"RESISTOR, European symbol";"";"";"";"";"";"";"";"";"";
"R8";"1k";"R-EU_M1206";"M1206";"RESISTOR, European symbol";"";"";"";"";"";"";"";"";"";
"R9";"1k";"R-EU_M1206";"M1206";"RESISTOR, European symbol";"";"";"";"";"";"";"";"";"";
"R10";"1k";"R-EU_M1206";"M1206";"RESISTOR, European symbol";"";"";"";"";"";"";"";"";"";
"R11";"1k";"R-EU_M1206";"M1206";"RESISTOR, European symbol";"";"";"";"";"";"";"";"";"";
"R12";"1k";"R-EU_M1206";"M1206";"RESISTOR, European symbol";"";"";"";"";"";"";"";"";"";
"R13";"1k";"R-EU_M1206";"M1206";"RESISTOR, European symbol";"";"";"";"";"";"";"";"";"";
"R14";"1k";"R-EU_M1206";"M1206";"RESISTOR, European symbol";"";"";"";"";"";"";"";"";"";
"R15";"8k";"R-EU_M1206";"M1206";"RESISTOR, European symbol";"";"";"";"";"";"";"";"";"";
"R16";"4k";"R-EU_M1206";"M1206";"RESISTOR, European symbol";"";"";"";"";"";"";"";"";"";
"R17";"2k";"R-EU_M1206";"M1206";"RESISTOR, European symbol";"";"";"";"";"";"";"";"";"";
"R18";"1k";"R-EU_M1206";"M1206";"RESISTOR, European symbol";"";"";"";"";"";"";"";"";"";
"R19";"1k";"R-EU_M1206";"M1206";"RESISTOR, European symbol";"";"";"";"";"";"";"";"";"";
"R20";"1k";"R-EU_M1206";"M1206";"RESISTOR, European symbol";"";"";"";"";"";"";"";"";"";
"R21";"8k";"R-EU_M1206";"M1206";"RESISTOR, European symbol";"";"";"";"";"";"";"";"";"";
"R22";"4k";"R-EU_M1206";"M1206";"RESISTOR, European symbol";"";"";"";"";"";"";"";"";"";
"R23";"2k";"R-EU_M1206";"M1206";"RESISTOR, European symbol";"";"";"";"";"";"";"";"";"";
"R24";"1k";"R-EU_M1206";"M1206";"RESISTOR, European symbol";"";"";"";"";"";"";"";"";"";
"R25";"1k";"R-EU_M1206";"M1206";"RESISTOR, European symbol";"";"";"";"";"";"";"";"";"";
"R26";"1k";"R-EU_M1206";"M1206";"RESISTOR, European symbol";"";"";"";"";"";"";"";"";"";
"R27";"1k";"R-EU_M1206";"M1206";"RESISTOR, European symbol";"";"";"";"";"";"";"";"";"";
"R28";"1k";"R-EU_M1206";"M1206";"RESISTOR, European symbol";"";"";"";"";"";"";"";"";"";
"R29";"8k";"R-EU_M1206";"M1206";"RESISTOR, European symbol";"";"";"";"";"";"";"";"";"";
"R30";"4k";"R-EU_M1206";"M1206";"RESISTOR, European symbol";"";"";"";"";"";"";"";"";"";
"R31";"2k";"R-EU_M1206";"M1206";"RESISTOR, European symbol";"";"";"";"";"";"";"";"";"";
"R32";"1k";"R-EU_M1206";"M1206";"RESISTOR, European symbol";"";"";"";"";"";"";"";"";"";
"R33";"1k";"R-EU_M1206";"M1206";"RESISTOR, European symbol";"";"";"";"";"";"";"";"";"";
"R34";"1k";"R-EU_M1206";"M1206";"RESISTOR, European symbol";"";"";"";"";"";"";"";"";"";
"R35";"8k";"R-EU_M1206";"M1206";"RESISTOR, European symbol";"";"";"";"";"";"";"";"";"";
"R36";"4k";"R-EU_M1206";"M1206";"RESISTOR, European symbol";"";"";"";"";"";"";"";"";"";
"R37";"2k";"R-EU_M1206";"M1206";"RESISTOR, European symbol";"";"";"";"";"";"";"";"";"";
"R38";"1k";"R-EU_M1206";"M1206";"RESISTOR, European symbol";"";"";"";"";"";"";"";"";"";
"R39";"1k";"R-EU_M1206";"M1206";"RESISTOR, European symbol";"";"";"";"";"";"";"";"";"";
"R40";"1k";"R-EU_M1206";"M1206";"RESISTOR, European symbol";"";"";"";"";"";"";"";"";"";
"R41";"1k";"R-EU_M1206";"M1206";"RESISTOR, European symbol";"";"";"";"";"";"";"";"";"";
"R42";"1k";"R-EU_M1206";"M1206";"RESISTOR, European symbol";"";"";"";"";"";"";"";"";"";
"U1";"AD8619ARZ";"AD8619ARZ";"SOIC127P600X175-14N";"Operational Amplifiers";"Good";"OP Amp Quad GP R-R I/O ???}2.5V/5V 14-Pin SOIC N Tube";"Analog Devices";"AD8619ARZ";"";"";"";"SOIC-14 Analog Devices";"1.96 USD";
"U2";"AD8619ARZ";"AD8619ARZ";"SOIC127P600X175-14N";"Operational Amplifiers";"Good";"OP Amp Quad GP R-R I/O ???}2.5V/5V 14-Pin SOIC N Tube";"Analog Devices";"AD8619ARZ";"";"";"";"SOIC-14 Analog Devices";"1.96 USD";
"U3";"AD8619ARZ";"AD8619ARZ";"SOIC127P600X175-14N";"Operational Amplifiers";"Good";"OP Amp Quad GP R-R I/O ???}2.5V/5V 14-Pin SOIC N Tube";"Analog Devices";"AD8619ARZ";"";"";"";"SOIC-14 Analog Devices";"1.96 USD";
"U4";"LM2681";"LM2681";"LM2681";"";"";"";"";"";"";"";"";"";"";
"U5";"TL7660P";"TL7660P";"DIL08";"CMOS VOLTAGE CONVERTER";"";"";"";"";"TL7660CP";"1755283";"14M2447";"";"";
"VDD";"";"PINHD-1X1";"1X01";"PIN HEADER";"";"";"";"";"";"";"";"";"";

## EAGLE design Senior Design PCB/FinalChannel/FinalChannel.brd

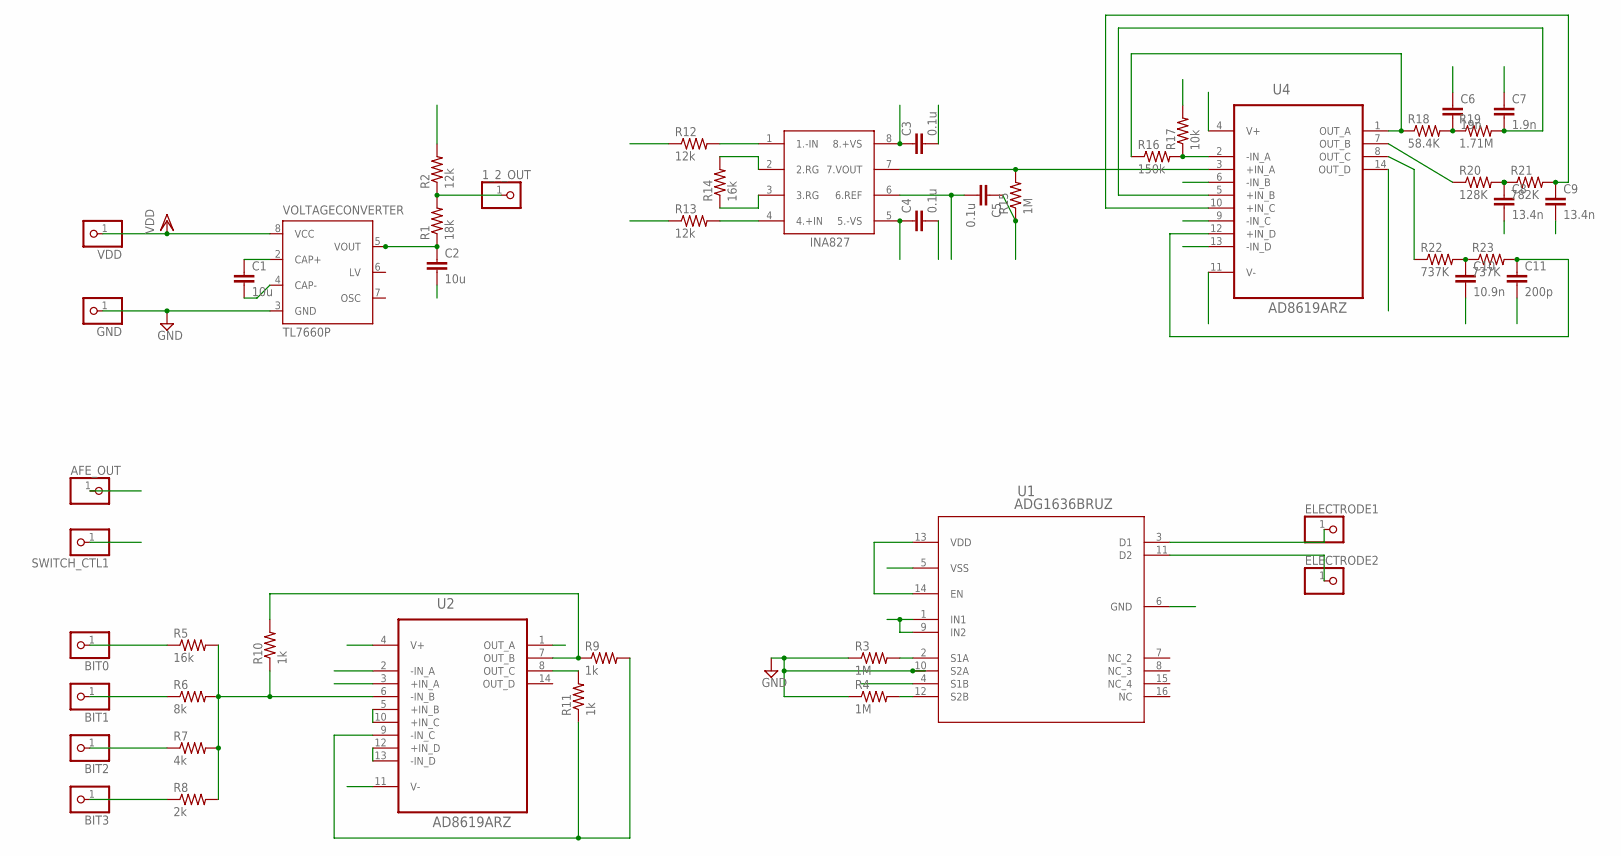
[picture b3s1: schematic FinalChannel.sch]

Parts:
1_2_OUT: PINHD-1X1; 1X01
AFE_OUT: PINHD-1X1; 1X01
BIT0, BIT1, BIT2, BIT3: PINHD-1X1; 1X01
C1, C2: 10u; C0805
C3, C4, C5: 0.1u; C0805
C6: 19n; C0805
C7: 1.9n; C0805
C8, C9: 13.4n; C0805
C10: 10.9n; C0805
C11: 200p; C0805
ELECTRODE1, ELECTRODE2: PINHD-1X1; 1X01
GND: PINHD-1X1; 1X01
INA1: INA827
R1: 18k; R0805
R2: 12k; R0805
R3, R4, R15: 1M; M0805
R5, R14: 16k; M0805
R6: 8k; M0805
R7: 4k; M0805
R8: 2k; M0805
R9, R10, R11: 1k; M0805
R12, R13: 12k; M0805
R16: 150k; M0805
R17: 10k; M0805
R18: 58.4K; M0805
R19: 1.71M; M0805
R20: 128K; M0805
R21: 782K; M0805
R22, R23: 737K; M0805
SWITCH_CTL1: PINHD-1X1; 1X01
U1: ADG1636BRUZ; RU_16
U2, U4: AD8619ARZ; SOIC127P600X175-14N
VDD: PINHD-1X1; 1X01
VOLTAGECONVERTER: TL7660P; DIL08

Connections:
1_2_OUT: 1_2_OUT.1, R1.2, R2.1
AFE_OUT: AFE_OUT.1, C10.2, U4.13 (-IN_D), U4.14 (OUT_D)
CTL1: SWITCH_CTL1.1, U1.1 (IN1), U1.9 (IN2)
E_1: ELECTRODE1.1, U1.3 (D1)
E_2: ELECTRODE2.1, U1.11 (D2)
GND: C2.2, C3.2, C4.2, C7.1, C9.2, C11.2, GND.1, R2.2, R3.1, R4.1, R17.2, U1.6 (GND), U1.10 (S2A), U2.3 (+IN_A), U2.5 (+IN_B), U2.10 (+IN_C), U2.12 (+IN_D), U2.13 (-IN_D), VOLTAGECONVERTER.3 (GND)
IN_N: R4.2, R12.1, U1.12 (S2B)
IN_P: R3.2, R13.1, U1.2 (S1A)
unnamed: C1.1, VOLTAGECONVERTER.2 (CAP+)
unnamed: C1.2, VOLTAGECONVERTER.4 (CAP-)
unnamed: R9.2, R11.1, U2.9 (-IN_C)
unnamed: INA1.1 (1.-IN), R12.2
unnamed: INA1.4 (4.+IN), R13.2
unnamed: BIT0.1, R5.1
unnamed: BIT1.1, R6.1
unnamed: BIT2.1, R7.1
unnamed: BIT3.1, R8.1
unnamed: R5.2, R6.2, R7.2, R8.2, R10.1, U2.6 (-IN_B)
unnamed: R9.1, R10.2, U2.7 (OUT_B)
unnamed: INA1.2 (2.RG), R14.2
unnamed: INA1.3 (3.RG), R14.1
unnamed: INA1.7 (7.VOUT), R15.2, U4.3 (+IN_A)
unnamed: R16.2, R17.1, U4.2 (-IN_A)
unnamed: R16.1, R18.1, U4.1 (OUT_A)
unnamed: C6.2, R18.2, R19.1
unnamed: C7.2, R19.2, U4.5 (+IN_B)
unnamed: C8.1, R20.2, R21.1
unnamed: C9.1, R21.2, U4.10 (+IN_C)
unnamed: C10.1, R22.2, R23.1
unnamed: C11.1, R23.2, U4.12 (+IN_D)
OUT_B: C6.1, R20.1, U4.6 (-IN_B), U4.7 (OUT_B)
OUT_C: C8.2, R22.1, U4.8 (OUT_C), U4.9 (-IN_C)
P_GEN_OUT: R11.2, U1.4 (S1B), U2.8 (OUT_C)
SINGLE-: C5.1, R15.1, U2.2 (-IN_A)
SINGLE_OUT: C5.2, INA1.6 (6.REF), U2.1 (OUT_A)
VDD: C3.1, INA1.8 (8.+VS), U1.13 (VDD), U1.14 (EN), U2.4 (V+), U4.4 (V+), VDD.1, VOLTAGECONVERTER.8 (VCC)
VDD-: C2.1, C4.1, INA1.5 (5.-VS), R1.1, U1.5 (VSS), U2.11 (V-), U4.11 (V-), VOLTAGECONVERTER.5 (VOUT)
